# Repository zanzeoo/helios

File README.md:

# helios
Hardware for Environmental Logging, IoT &amp; Outdoor Sensors

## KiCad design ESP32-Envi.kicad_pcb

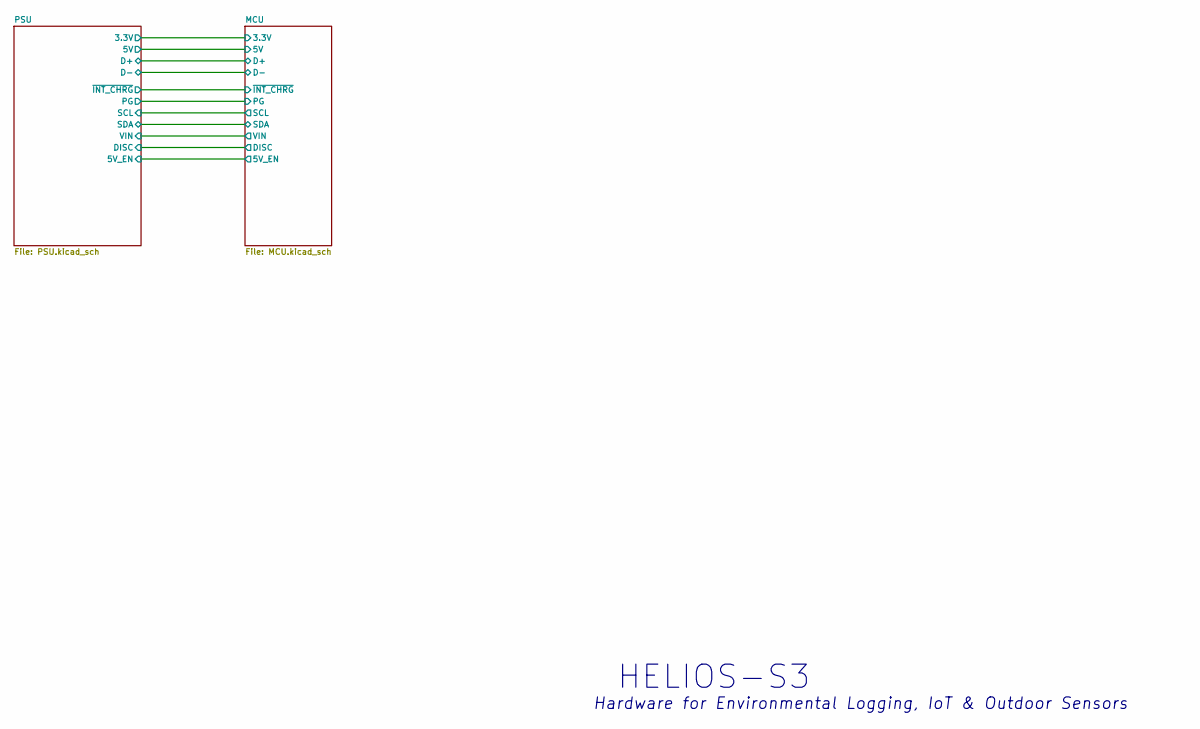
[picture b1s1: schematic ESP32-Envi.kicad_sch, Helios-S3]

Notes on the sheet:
HELIOS-S3
Hardware for Environmental Logging, IoT & Outdoor Sensors

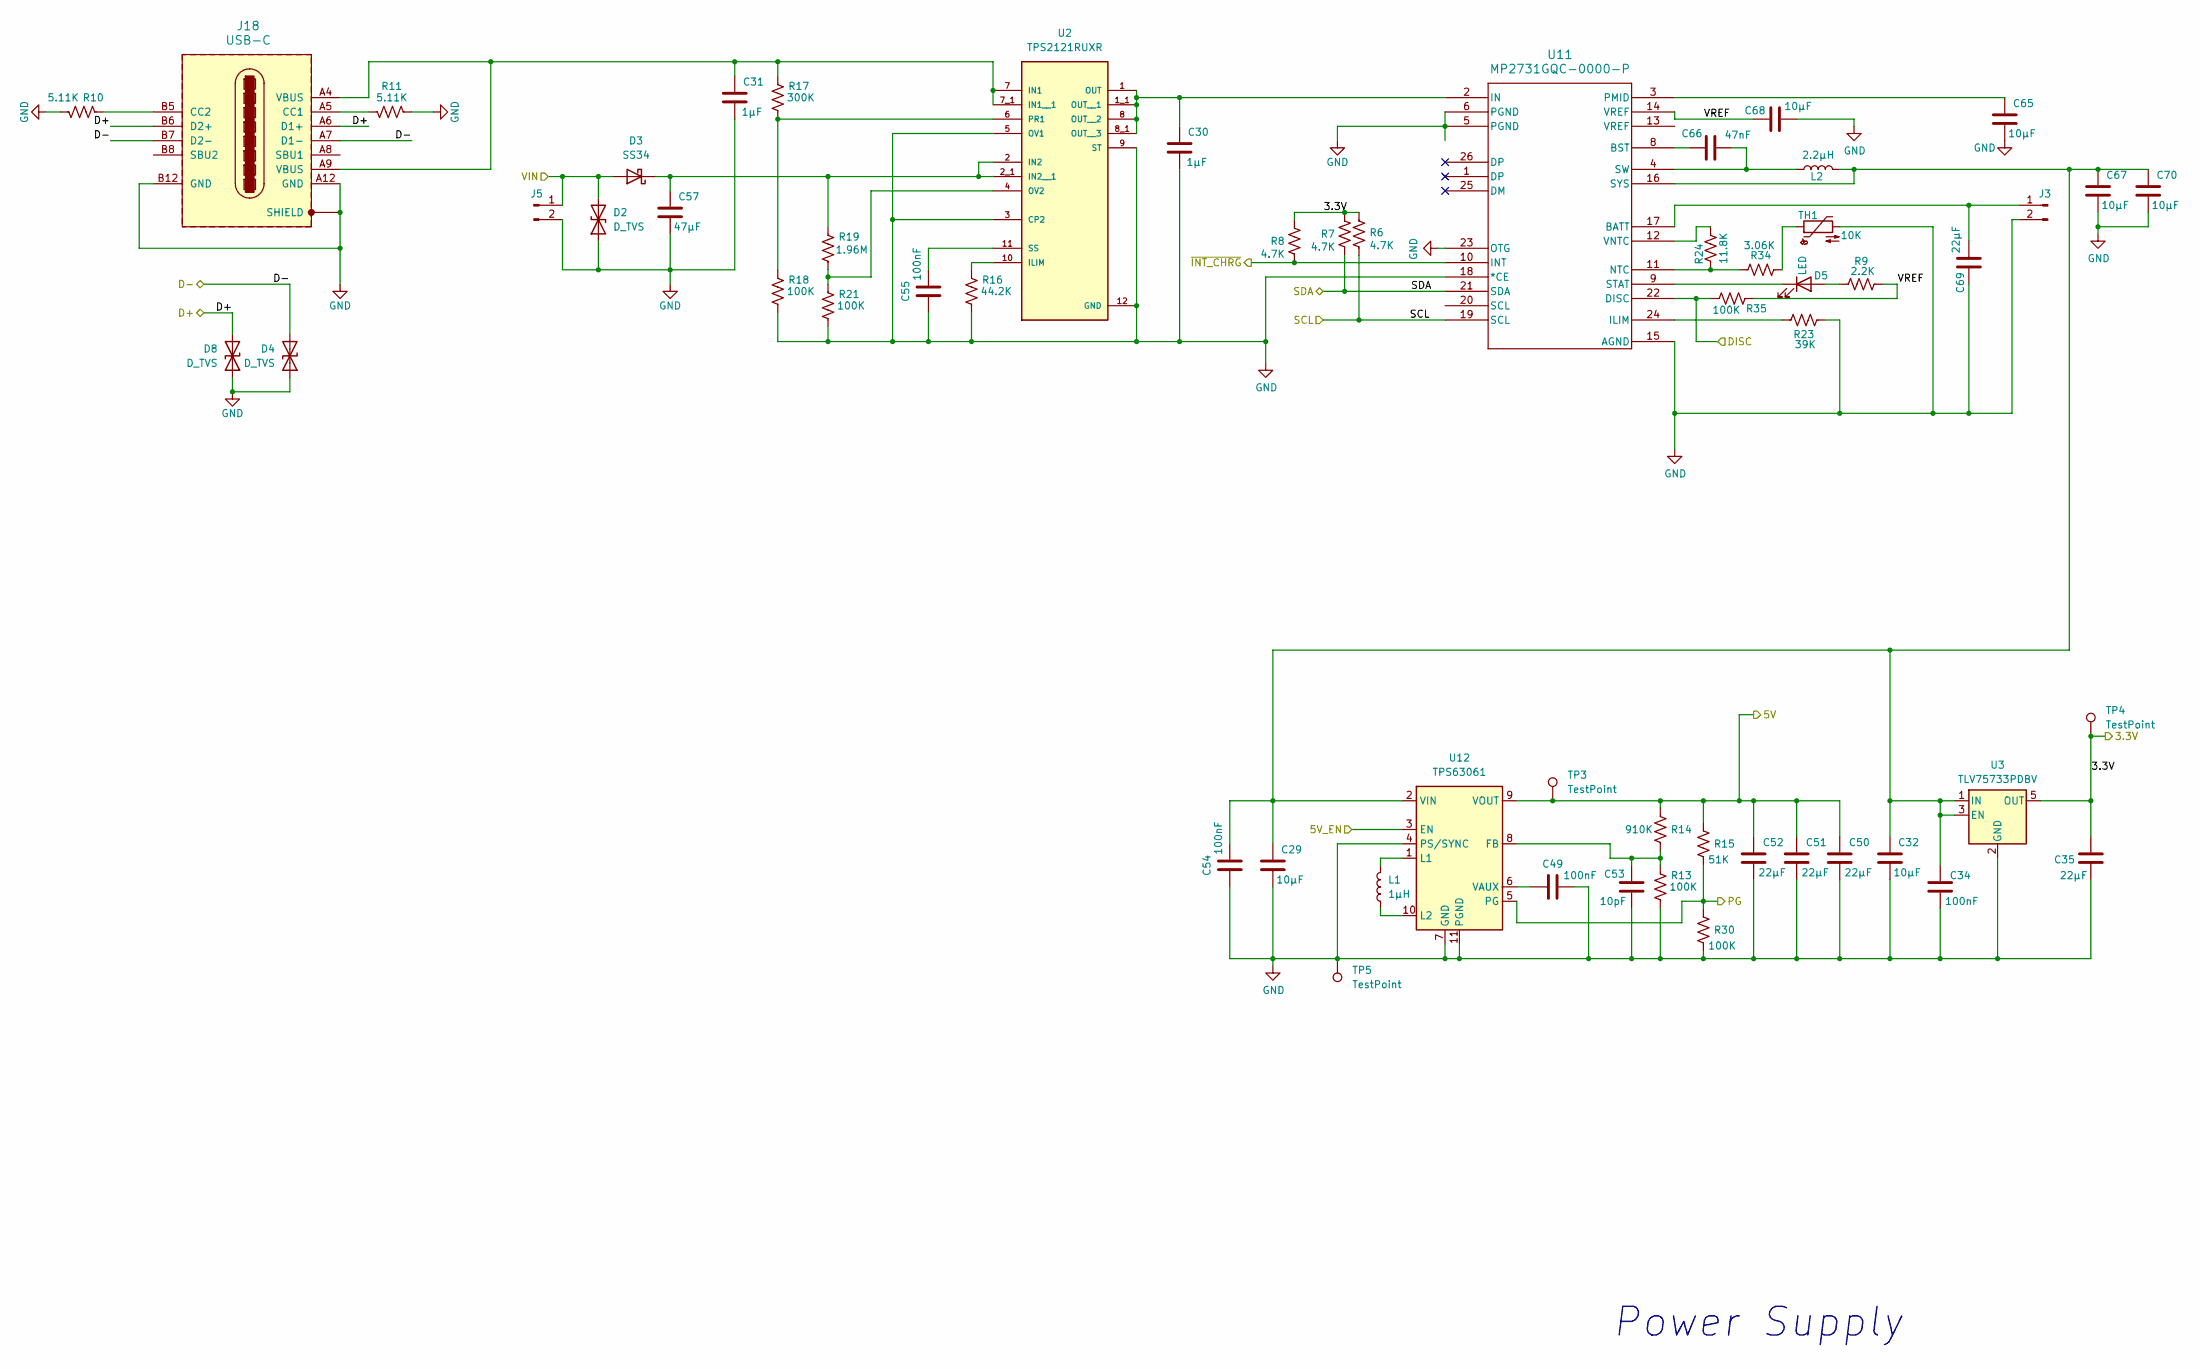
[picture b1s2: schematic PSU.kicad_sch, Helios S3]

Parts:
C29, C32, C68: 10µF; C_0603_1608Metric_Pad1.08x0.95mm_HandSolder
C30, C31: 1µF; C_0805_2012Metric_Pad1.18x1.45mm_HandSolder
C34, C49, C54, C55: 100nF; C_0603_1608Metric
C35, C50, C51, C52: 22µF; C_0603_1608Metric_Pad1.08x0.95mm_HandSolder
C53: 10pF; C_0603_1608Metric
C57: 47µF; C_1210_3225Metric_Pad1.33x2.70mm_HandSolder
C65: 10µF; C_0805_2012Metric_Pad1.18x1.45mm_HandSolder; Voltage 35V
C66: 47nF; C_0603_1608Metric
C67, C70: 10µF; C_0805_2012Metric_Pad1.18x1.45mm_HandSolder
C69: 22µF; C_0805_2012Metric_Pad1.18x1.45mm_HandSolder
D2, D4, D8: D_TVS; D_SOD-323_HandSoldering
D3: SS34; D_SMA
D5: LED; LED_0603_1608Metric_Pad1.05x0.95mm_HandSolder
J3, J5: Conn_01x02_Pin; JST_PH_B2B-PH-K_1x02_P2.00mm_Vertical
J18: USB-C; USB_C_Receptacle_G-Switch_GT-USB-7010ASV
L1: 1µH; L_Coilcraft_XxL4020
L2: 2.2µH; L_Coilcraft_XxL4020
R6, R7, R8: 4.7K; R_0603_1608Metric_Pad0.98x0.95mm_HandSolder
R9: 2.2K; R_0603_1608Metric_Pad0.98x0.95mm_HandSolder
R10, R11: 5.11K; R_0603_1608Metric_Pad0.98x0.95mm_HandSolder
R13, R18, R21, R30, R35: 100K; R_0603_1608Metric_Pad0.98x0.95mm_HandSolder
R14: 910K; R_0603_1608Metric_Pad0.98x0.95mm_HandSolder
R15: 51K; R_0603_1608Metric_Pad0.98x0.95mm_HandSolder
R16: 44.2K; R_0603_1608Metric_Pad0.98x0.95mm_HandSolder
R17: 300K; R_0603_1608Metric_Pad0.98x0.95mm_HandSolder
R19: 1.96M; R_0603_1608Metric_Pad0.98x0.95mm_HandSolder
R23: 39K; R_0603_1608Metric_Pad0.98x0.95mm_HandSolder
R24: 11.8K; R_0603_1608Metric_Pad0.98x0.95mm_HandSolder
R34: 3.06K; R_0603_1608Metric_Pad0.98x0.95mm_HandSolder
TH1: 10K; R_0805_2012Metric_Pad1.20x1.40mm_HandSolder
TP3, TP4: TestPoint; TestPoint_Pad_1.0x1.0mm
TP5: TestPoint; TestPoint_Keystone_5019_Miniature
U2: TPS2121RUXR; IC_TPS2121RUXR; MPN TPS2121RUXR
U3: TLV75733PDBV; SOT-23-5
U11: MP2731GQC-0000-P; QFN-26_MP2731
U12: TPS63061; Texas_S-PWSON-N10_ThermalVias

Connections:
/MCU/3.3V: C35.1, R6.1, R7.1, R8.1, TP4.1 (1_1), U3.5 (OUT); also elsewhere on the board
/MCU/5V: C50.1, C51.1, C52.1, R14.1, R15.1, TP3.1 (1_1), U12.9 (VOUT); also elsewhere on the board
/MCU/5V_EN: U12.3 (EN); also elsewhere on the board
/MCU/D+: D8.2 (A2), J18.A6 (D1+), J18.B6 (D2+); also elsewhere on the board
/MCU/D-: D4.2 (A2), J18.A7 (D1-), J18.B7 (D2-); also elsewhere on the board
/MCU/DISC: R35.2, U11.22 (DISC); also elsewhere on the board
/MCU/IO6: R7.2, U11.21 (SDA); also elsewhere on the board
/MCU/IO7: R6.2, U11.19 (SCL); also elsewhere on the board
/MCU/PG: R15.2, R30.1, U12.5 (PG); also elsewhere on the board
/MCU/VIN: D2.2 (A2), D3.2 (A), J5.1; also elsewhere on the board
/MCU/~INT_CHRG: R8.2, U11.10 (INT); also elsewhere on the board
/PSU/VREF: C68.2, R9.2, R35.1, U11.14 (VREF)
GND: C29.1, C30.1, C31.1, C32.1, C34.1, C35.2, C49.1, C50.2, C51.2, C52.2, C53.2, C54.2, C55.2, C57.1, C65.1, C67.1, C68.1, C69.2, C70.1, D2.1 (A1), D4.1 (A1), D8.1 (A1), J3.2, J5.2, J18.A12 (GND), J18.B12 (GND), J18.SH (SHIELD), R10.1, R11.2, R13.2, R16.2, R18.2, R21.2, R23.2, R30.2, TH1.2, TP5.1 (1_1), U2.3 (CP2), U2.5 (OV1), U2.9 (ST), U2.12 (GND), U3.2 (GND), U11.5 (PGND), U11.6 (PGND), U11.7 (PGND), U11.15 (AGND), U11.18 (*CE), U11.23 (OTG), U12.4 (PS/SYNC), U12.7 (GND), U12.11 (PGND); also elsewhere on the board
unnamed: C57.2, D3.1 (K), R19.1, U2.2 (IN2), U2.2_1 (IN2__1)
unnamed: D5.2 (A), R9.1
unnamed: D5.1 (K), U11.9 (STAT)
unnamed: C69.1, J3.1, U11.17 (BATT)
unnamed: J18.A5 (CC1), R11.1
unnamed: J18.B5 (CC2), R10.2
unnamed: R34.1, TH1.1
unnamed: R16.1, U2.10 (ILIM)
unnamed: C31.2, J18.A4 (VBUS), J18.A9 (VBUS), R17.1, U2.7 (IN1), U2.7_1 (IN1__1)
unnamed: R19.2, R21.1, U2.4 (OV2)
unnamed: R17.2, R18.1, U2.6 (PR1)
unnamed: C55.1, U2.11 (SS)
unnamed: C66.2, U11.8 (BST)
unnamed: R23.1, U11.24 (ILIM)
unnamed: C30.2, U2.1 (OUT), U2.1_1 (OUT__1), U2.8 (OUT__2), U2.8_1 (OUT__3), U11.2 (IN)
unnamed: R24.1, R34.2, U11.11 (NTC)
unnamed: C65.2, U11.3 (PMID)
unnamed: C66.1, L2.1, U11.4 (SW)
unnamed: C29.2, C32.2, C34.2, C54.1, C67.2, C70.2, L2.2, U3.1 (IN), U3.3 (EN), U11.16 (SYS), U12.2 (VIN)
unnamed: R24.2, U11.12 (VNTC)
unnamed: C53.1, R13.1, R14.2, U12.8 (FB)
unnamed: L1.2, U12.1 (L1)
unnamed: L1.1, U12.10 (L2)
unnamed: C49.2, U12.6 (VAUX)

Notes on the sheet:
Power Supply

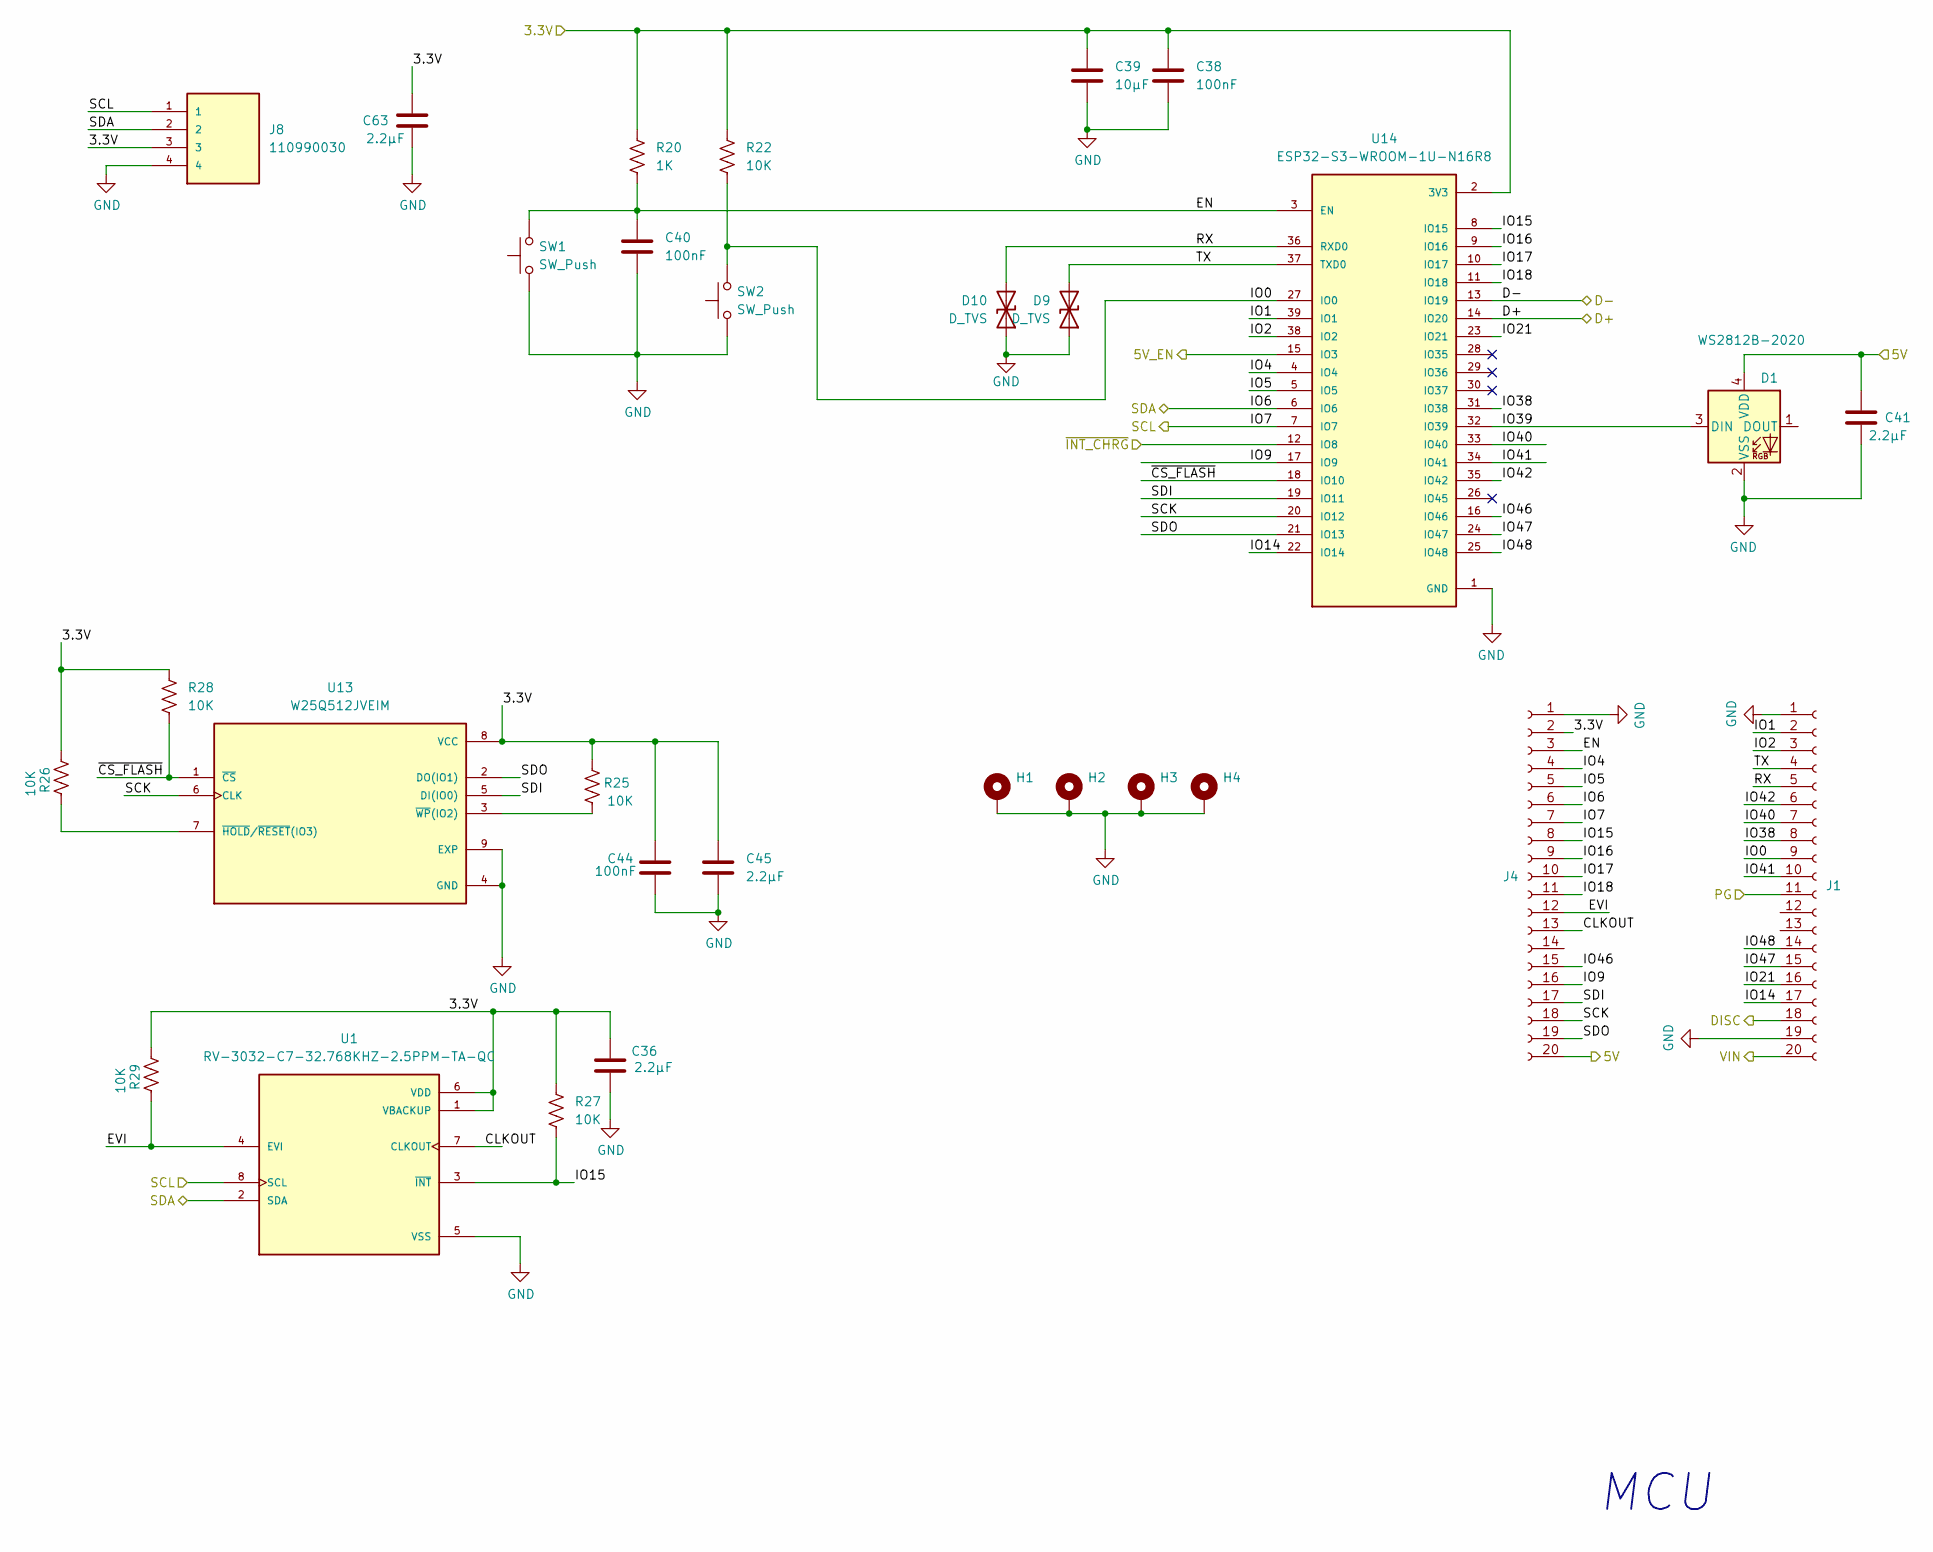
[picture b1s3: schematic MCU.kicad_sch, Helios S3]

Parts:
C36, C41, C45, C63: 2.2µF; C_0603_1608Metric_Pad1.08x0.95mm_HandSolder
C38, C40, C44: 100nF; C_0603_1608Metric_Pad1.08x0.95mm_HandSolder
C39: 10µF; C_0603_1608Metric_Pad1.08x0.95mm_HandSolder
D1: WS2812B-2020; LED_WS2812B-2020_PLCC4_2.0x2.0mm
D9, D10: D_TVS; D_SOD-323_HandSoldering
H1, H2, H3, H4: MountingHole_Pad; MountingHole_2.5mm_Pad_TopBottom
J1, J4: Conn_01x20_Socket; PinHeader_1x20_P2.54mm_Vertical
J8: 110990030; JST_GH_BM04B-GHS-TBT_1x04-1MP_P1.25mm_Vertical; PARTREV A
R20: 1K; R_0603_1608Metric_Pad0.98x0.95mm_HandSolder
R22, R25, R26, R27, R28, R29: 10K; R_0603_1608Metric_Pad0.98x0.95mm_HandSolder
SW1, SW2: SW_Push; SW_Push_1P1T_NO_CK_KMR2
U1: RV-3032-C7-32.768KHZ-2.5PPM-TA-QC; MicroCrystal_C7_SON-8_1.5x3.2mm_P0.9mm; MPN RV-3032-C7-32.768KHZ-2.5PPM-TA-QC
U13: W25Q512JVEIM; SON127P600X800X80-9N; PARTREV D
U14: ESP32-S3-WROOM-1U-N16R8; XCVR_ESP32-S3-WROOM-1U-N16R8; PARTREV v1.1

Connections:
/MCU/3.3V: C36.2, C38.1, C39.1, C44.1, C45.1, C63.1, J4.2, J8.3, R20.2, R22.2, R25.2, R26.2, R27.1, R28.1, R29.2, U1.1 (VBACKUP), U1.6 (VDD), U13.8 (VCC), U14.2 (3V3); also elsewhere on the board
/MCU/5V: C41.1, D1.4 (VDD), J4.20; also elsewhere on the board
/MCU/5V_EN: U14.15 (IO3); also elsewhere on the board
/MCU/CLKOUT: J4.13, U1.7 (CLKOUT)
/MCU/D+: U14.14 (IO20); also elsewhere on the board
/MCU/D-: U14.13 (IO19); also elsewhere on the board
/MCU/DISC: J1.18; also elsewhere on the board
/MCU/EN: C40.1, J4.3, R20.1, SW1.2, U14.3 (EN)
/MCU/EVI: J4.12, R29.1, U1.4 (EVI)
/MCU/IO0: J1.9, R22.1, SW2.2, U14.27 (IO0)
/MCU/IO1: J1.2, U14.39 (IO1)
/MCU/IO2: J1.3, U14.38 (IO2)
/MCU/IO4: J4.4, U14.4 (IO4)
/MCU/IO5: J4.5, U14.5 (IO5)
/MCU/IO6: J4.6, J8.2, U1.2 (SDA), U14.6 (IO6); also elsewhere on the board
/MCU/IO7: J4.7, J8.1, U1.8 (SCL), U14.7 (IO7); also elsewhere on the board
/MCU/IO9: J4.16, U14.17 (IO9)
/MCU/IO14: J1.17, U14.22 (IO14)
/MCU/IO15: J4.8, R27.2, U1.3 (~INT), U14.8 (IO15)
/MCU/IO16: J4.9, U14.9 (IO16)
/MCU/IO17: J4.10, U14.10 (IO17)
/MCU/IO18: J4.11, U14.11 (IO18)
/MCU/IO21: J1.16, U14.23 (IO21)
/MCU/IO38: J1.8, U14.31 (IO38)
/MCU/IO39: D1.3 (DIN), U14.32 (IO39)
/MCU/IO40: J1.7, U14.33 (IO40)
/MCU/IO41: J1.10, U14.34 (IO41)
/MCU/IO42: J1.6, U14.35 (IO42)
/MCU/IO46: J4.15, U14.16 (IO46)
/MCU/IO47: J1.15, U14.24 (IO47)
/MCU/IO48: J1.14, U14.25 (IO48)
/MCU/PG: J1.11; also elsewhere on the board
/MCU/RX: D10.2 (A2), J1.5, U14.36 (RXD0)
/MCU/SCK: J4.18, U13.6 (CLK), U14.20 (IO12)
/MCU/SDI: J4.17, U13.5 (DI(IO0)), U14.19 (IO11)
/MCU/SDO: J4.19, U13.2 (DO(IO1)), U14.21 (IO13)
/MCU/TX: D9.2 (A2), J1.4, U14.37 (TXD0)
/MCU/VIN: J1.20; also elsewhere on the board
/MCU/~CS_FLASH: R28.2, U13.1 (~CS), U14.18 (IO10)
/MCU/~INT_CHRG: U14.12 (IO8); also elsewhere on the board
GND: C36.1, C38.2, C39.2, C40.2, C41.2, C44.2, C45.2, C63.2, D1.2 (VSS), D9.1 (A1), D10.1 (A1), H1.1 (1_1), H2.1 (1_1), H3.1 (1_1), H4.1 (1_1), J1.1, J1.19, J4.1, J8.4, SW1.1, SW2.1, U1.5 (VSS), U13.4 (GND), U13.9 (EXP), U14.1 (GND), U14.40 (GND), U14.41_1 (GND), U14.41_2 (GND), U14.41_3 (GND), U14.41_4 (GND), U14.41_5 (GND), U14.41_6 (GND), U14.41_7 (GND), U14.41_8 (GND), U14.41_9 (GND); also elsewhere on the board
unnamed: R26.1, U13.7 (~HOLD/~RESET(IO3))
unnamed: R25.1, U13.3 (~WP(IO2))

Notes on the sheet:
MCU

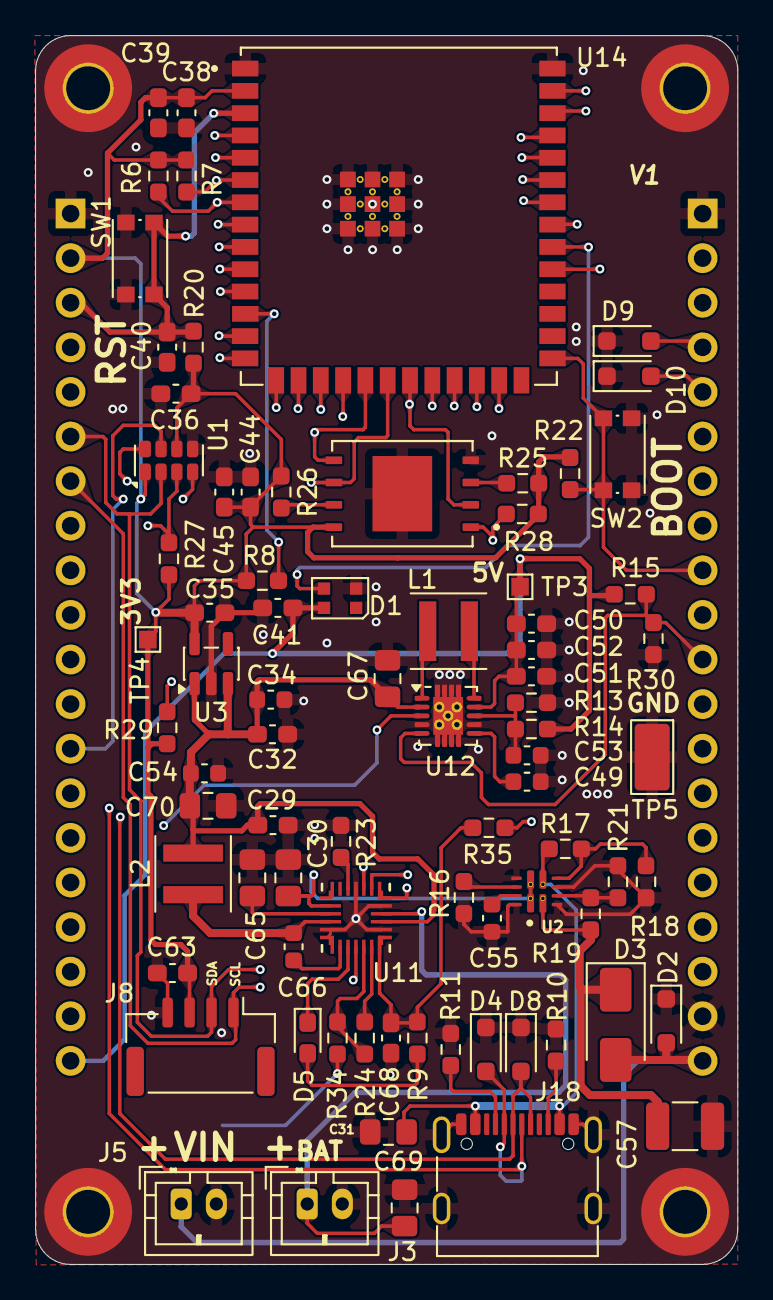
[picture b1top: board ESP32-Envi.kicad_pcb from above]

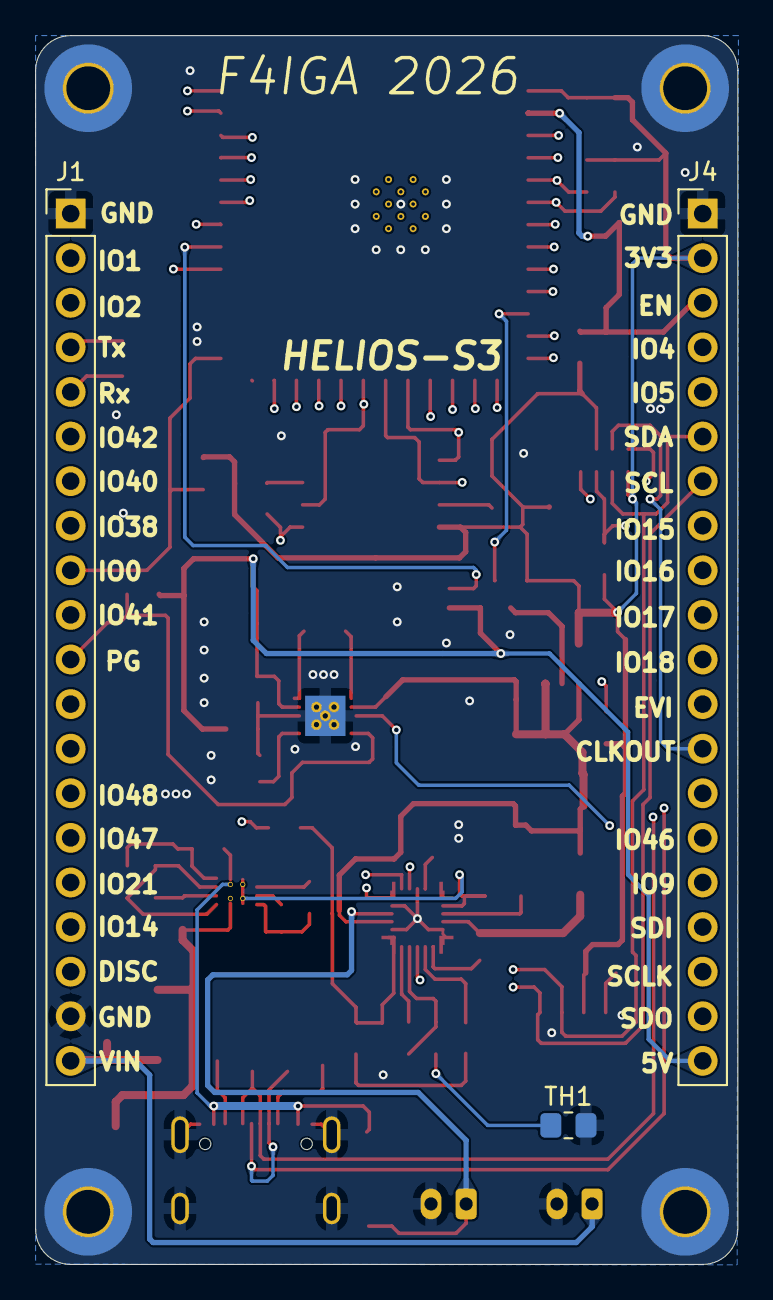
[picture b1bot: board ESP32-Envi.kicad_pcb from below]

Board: 4 copper layers, 40.0 x 70.0 mm, 87 parts (3 on the bottom side), 68 nets.
